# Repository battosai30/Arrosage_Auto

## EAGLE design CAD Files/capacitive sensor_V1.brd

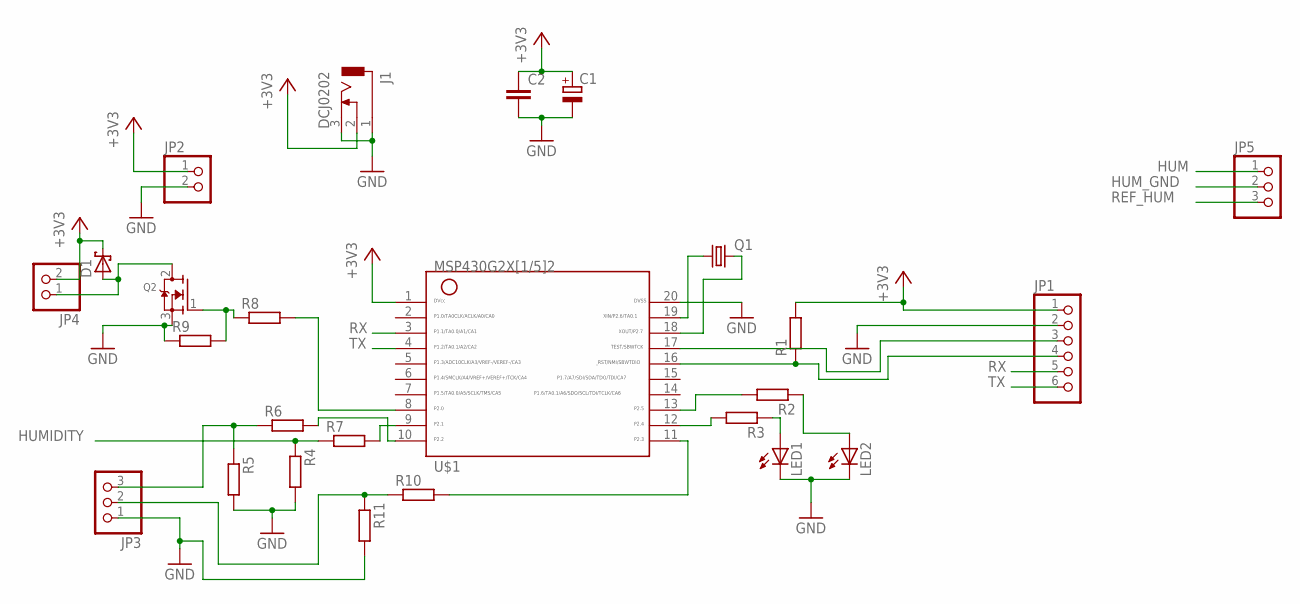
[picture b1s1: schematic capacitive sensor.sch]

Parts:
C1: CPOL-EUE5-8.5; E5-8,5
C2: C-EU025-030X050; C025-030X050
D1: SCHOTTKY-DIODEDO41-7; DO41-7
J1: DCJ0202
JP1: HEADER-1X6; 1X06_OVAL
JP2, JP4: HEADER-1X2; 1X02_OVAL
JP3, JP5: PINHD-1X3; 1X03
LED1, LED2: LED3MM
Q1: CRYSTALTC26H; TC26H
Q2: MOSFET-NGDS_TO220V; TO220V
R1, R2, R3, R4, R5, R6, R7, R8, R9, R10, R11: R-EU_0204/7; 0204/7
U$1: G2X[1/5]2---N20; N20

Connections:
+3V3: C1.+, C2.1, D1.C, J1.2, JP1.1, JP2.1, JP4.2, R1.2, U$1.1
GND: C1.-, C2.2, J1.1, J1.3, JP1.2, JP2.2, JP3.1, LED1.K (C), LED2.K (C), Q2.3 (S), R4.2, R5.2, R9.1, R11.2, U$1.20
HUM: JP5.1
HUMIDITY: R4.1, R7.1
HUM_GND: JP5.2
unnamed: JP1.3, U$1.17
unnamed: JP1.4, R1.1, U$1.16
unnamed: Q1.1, U$1.19
unnamed: LED1.A, R3.1
unnamed: R3.2, U$1.12
unnamed: R2.2, U$1.13
unnamed: LED2.A, R2.1
unnamed: R7.2, U$1.9
unnamed: R6.2, U$1.10
unnamed: JP3.3, R5.1, R6.1
unnamed: Q1.2, U$1.18
unnamed: D1.A, JP4.1, Q2.2 (D)
unnamed: Q2.1 (G), R8.1, R9.2
unnamed: R8.2, U$1.8
unnamed: JP3.2, R10.1, R11.1
unnamed: R10.2, U$1.11
REF_HUM: JP5.3
RX: JP1.5, U$1.3
TX: JP1.6, U$1.4

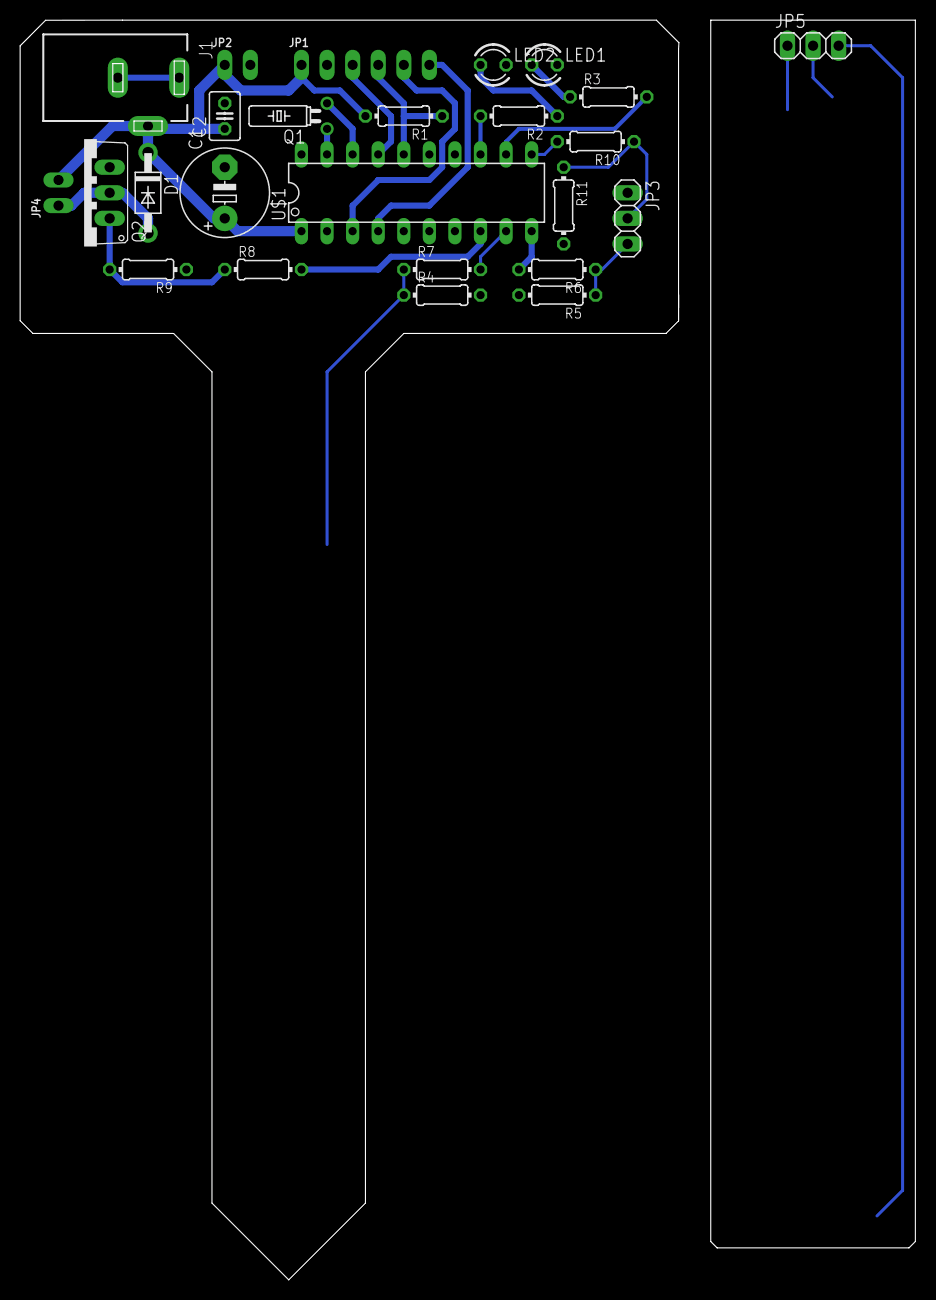
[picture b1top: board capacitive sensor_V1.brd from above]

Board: 2 copper layers, 88.9 x 125.1 mm, 25 parts (0 on the bottom side), 21 nets.

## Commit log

2015-06-23 :space_invader: Added .gitattributes & .gitignore files
2015-06-23 First release

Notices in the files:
parts and their libraries:
microbuilder: This work is placed in the public domain, and may be freely used for commercial and non-commercial work with the following conditions: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
